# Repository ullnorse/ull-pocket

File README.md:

# ull-pocket

A pocket environment meter and learning board: ESP32-C6, temperature/humidity, pressure and motion sensors, a 1.54" e-paper display and a 1200 mAh LiPo. It sleeps most of the time; buttons, motion or a timer wake it, and Wi-Fi only runs when the firmware asks for it.

## Hardware

| Block | Part |
|---|---|
| MCU | ESP32-C6-MINI-1-N4 (Wi-Fi 6, BLE, 802.15.4, 4 MB flash) |
| Temperature / humidity | Sensirion SHT40, on a moated island away from the heat sources |
| Pressure | Bosch BMP580 |
| Motion / wake | ST LIS2DW12 accelerometer |
| Battery | 1200 mAh 1S LiPo (103040), 1.25 mm plug; MAX17048 fuel gauge; low-side reverse-polarity FET |
| Charging | TI BQ24073 power path, ~270 mA from USB-C, about 5-6 h for a full charge |
| 3.3 V | Richtek RT9080 LDO, ~2 uA quiescent |
| Display | Good Display GDEY0154D67, 200x200 black/white e-paper, SSD1681, bought separately |
| Input | 3 side buttons UP / OK / DN (UP and OK wake from deep sleep; DN doubles as BOOT) |
| LEDs | Power (green), charge (red), user (red/blue), side-view at the bottom edge |
| Programming | USB-C (native USB Serial/JTAG) or 2x3 pogo pads on the back |

Board: 40 x 44.5 mm, 4 layers, 1.6 mm (JLC04161H-3313 stackup), all parts on the front; the panel sits on the back.

## Files

| Path | Contents |
|---|---|
| `ull-pocket.kicad_pro` | KiCad 10 project (schematic + board) |
| `lib/` | Project symbols, footprints and 3D models |
| `production/` | JLCPCB Gerbers, BOM and CPL: single board (`ull-pocket-r0.9-*`) and the assembly panel (`ull-pocket-r0.9-panel-*`, made by `tools/panelize.sh`) |
| `PARTS.md` | Parts list with LCSC numbers and design notes |
| `DATASHEETS.md` | Datasheet links |
| `docs/mechanical.md` | Outline, keep-outs, panel, battery and button positions for a case |
| `docs/3d-models.md` | 3D models checked against the datasheets |
| `production/ull-pocket-r0.9-assembly.pdf` | Assembly drawing: every part with its reference. The silkscreen labels ICs, connectors, buttons, LEDs and test points only; look resistors and capacitors up here |
| `docs/learn.html` | Interactive course: understand every part of the board, from zero |
| `docs/best-practices.md` | Schematic, layout, DFM and silkscreen checklist with sources, and how this board was checked against it |
| `tools/` | Checks and exports: ERC and netlist checks, JLC export, renders (`tools/archive/` holds the retired schematic generator) |

## Ordering

Order the **panel**: one board with 5 mm rails on the left and right (tooling holes and fiducials) and mouse-bite tabs, made by `tools/panelize.sh` (needs KiKit). The rails are only left and right because parts overhang the top and bottom edges; JLC's own rails could collide with them.

1. Upload `production/ull-pocket-r0.9-panel-gerbers.zip` to JLCPCB and set:
   - 4 layers, 1.6 mm, stackup JLC04161H-3313, impedance control not needed
   - surface finish **ENIG** (the LGA/QFN/DFN parts need a flat finish; HASL is the default)
   - min via hole / diameter **0.2 / 0.45 mm**; via covering: tented
   - order number: **specify a position** (the `JLCJLCJLCJLC` text on the front silkscreen)
   - panel by customer (1 board per panel), edge rails: none (already in the files)
2. Enable PCB assembly (top side, **Standard PCBA**: U1, U3, U4 and the LEDs aren't offered on Economic) and upload `ull-pocket-r0.9-panel-bom.csv` and `ull-pocket-r0.9-panel-cpl.csv`.
3. Add a remark: "Customer panel with left/right rails and mouse bites. Components overhang the board edge: ESP32 module antenna 5.4 mm (top edge), USB-C 0.6 mm, D1/D5 LEDs 0.4 mm and RGB D6 0.65 mm (bottom edge), side buttons 0.2 mm (left edge)."
4. Check the part rotations in JLC's preview against `production/rotation-check.md`, and D1/D5/D6 against `docs/3d-models.md` (lens toward the board edge, cathode on pad 1).
5. Buy separately: the e-paper panel (GDEY0154D67), a 103040 LiPo with a protection board and 1.25 mm plug (check that it mates with J2 and its polarity: pin 2 = +), and a 3 mm thermal gap pad for TH1 (see `docs/mechanical.md`).
6. Separate boards from the rails by cutting the tabs, not bending: U1's pads and the VBAT track are about 1 mm from the holes.
7. Before first USB plug-in, check the cell's polarity. Q2 blocks a reversed cell on battery, but with USB in the charger slowly drains it through Q2.

## Programming

Plug in USB-C. The ESP32-C6 shows up as a USB serial port and esptool, Arduino or ESP-IDF flash it with no buttons: target `esp32c6` (Arduino: "ESP32C6 Dev Module", USB CDC On Boot enabled).

USB is off while the chip is in deep sleep, so keep the firmware awake while `USB_PGOOD_N` (IO1) is low (cable plugged in).

Firmware rules:
- Stop at a safe cell voltage: the cell's listing doesn't promise over-discharge protection.
- Enable the RTC watchdog: EN is only on the back pogo pads, so there's no reset button in the case.
- IO15 (CHG_DIS) high pauses charging. In deep sleep, hold it low or leave it as an input so R36 keeps charging on.
- Don't run Wi-Fi validation with no cell: the input limit leaves little margin over TX peaks.
- Ignore temperature and humidity while charging and until the case cools; measure how long that takes on the first board.

First-board power-up:
1. Power up without the panel. Check +3V3 at TP5.
2. Unpower the board, plug the panel in, and check continuity from GND (TP3) to the panel's VSS finger, the 17th from the pin-1 end. It must beep: a reversed tail would put about 20 V on the wrong panel pins.
3. Only then power up with the panel.

First-board charge test: compare TH1 with a thermocouple on the cell during a full charge. Board heat could still reach TH1's 47 C limit in a very warm room and pause charging (estimated, not measured). CHG flashing at 2 Hz means a timer fault; replug USB to clear it.

**Recovery:** if the firmware crashes, sleeps or disables USB before it can be flashed, unplug USB and the battery, hold **DN** (it is also BOOT, IO9), and plug USB back in. The chip starts in its ROM download mode; flash as usual, then reset by unplugging. The back pogo pads (J4) carry EN, BOOT and UART0 for a pogo fixture.

## Opening in KiCad

### 1. Install KiCad 10

Download KiCad 10.0 or newer from [kicad.org/download](https://www.kicad.org/download/) and use the default install, which includes the standard symbol, footprint and 3D-model libraries. KiCad 9 and older cannot open these files.

- **Windows / macOS:** run the installer.
- **Ubuntu / Debian:**
  ```sh
  sudo add-apt-repository ppa:kicad/kicad-10.0-releases
  sudo apt install kicad kicad-footprints kicad-symbols kicad-packages3d
  ```
  `kicad-packages3d` is needed for the 3D viewer.

On the very first start KiCad asks how to configure the global library tables: choose **Copy default global library table**.

### 2. Get the files

```sh
git clone https://github.com/ullnorse/ull-pocket.git
```

or use **Code → Download ZIP** on GitHub and unzip it.

### 3. Open the project

Open `ull-pocket.kicad_pro` (double-click it, or **File → Open Project** in KiCad). From the project window:

- **Schematic Editor** shows the schematic (one A3 sheet).
- **PCB Editor** shows the board. **View → 3D Viewer** (Alt+3) shows the assembled board.

No library setup is needed. The project's own symbols, footprints and 3D models are in `lib/` and are registered by the project-level `sym-lib-table` and `fp-lib-table` (paths are relative, via `${KIPRJMOD}`). Everything else comes from KiCad's standard libraries.

Keep the folder structure intact: KiCad finds `lib/` relative to the `.kicad_pro` file. If footprints or 3D models show as missing, check **Preferences → Manage Footprint Libraries → Project Specific Libraries** lists `ull-pocket` and that the folder was not moved.

### 4. Editing

- **Board:** edit freely in the PCB Editor. Run **Inspect → Design Rules Checker** before ordering. Custom rules are in `ull-pocket.kicad_dru` (side-LED edge clearance, e-paper high-voltage clearance, the thin traces on the SHT40 island, U6 thermal vias). Expect 3 harmless "footprint does not match library" warnings (C12, U1, J1) for parts edited on purpose.
- **Schematic and symbols:** edit them in the Schematic Editor and Symbol Editor. The project's symbols are in `lib/ull-pocket.kicad_sym`.
- After a schematic change, update the board with **Tools → Update PCB from Schematic** (F8) in the PCB Editor.

### 5. Regenerating production files

In KiCad: **File → Fabrication Outputs** (Gerbers, drill files, component placement). The JLCPCB-formatted files in `production/` are made by scripts, on Linux with KiCad 10 and Python 3:

```sh
sh tools/jlc_export.sh                     # Gerbers + drill files -> production/*-gerbers.zip
python3 tools/jlc_cpl.py ull-pocket.kicad_pcb <easyeda-cache> production   # BOM + CPL with JLC rotations
sh tools/panelize.sh                       # assembly panel -> build/panel/ull-pocket-panel.kicad_pcb (pipx install kikit)
sh tools/jlc_export.sh build/panel/ull-pocket-panel.kicad_pcb ull-pocket-r0.9-panel
python3 tools/jlc_cpl.py build/panel/ull-pocket-panel.kicad_pcb <easyeda-cache> production ull-pocket-r0.9-panel
python3 tools/silk/assembly.py ull-pocket.kicad_pcb production/ull-pocket-r0.9-assembly.pdf
sh tools/check_sch.sh                      # ERC, netlist checks, pin/pad checks, schematic PDF + PNG
sh tools/render3d.sh                       # 3D renders -> build/render3d/
```

`jlc_cpl.py` compares each footprint with JLC's own (EasyEDA) footprint to get placement rotations; fetch those once per LCSC part with `easyeda2kicad --footprint --lcsc_id=Cxxx --output=<easyeda-cache>/Cxxx/lib` (`pip install easyeda2kicad`). `check_sch.sh` also needs `rsvg-convert` (`sudo apt install librsvg2-bin`). `tools/check_net.py` encodes the intended connections; update it when you change the circuit on purpose.

## License

CERN-OHL-P v2, see [LICENSE](LICENSE).

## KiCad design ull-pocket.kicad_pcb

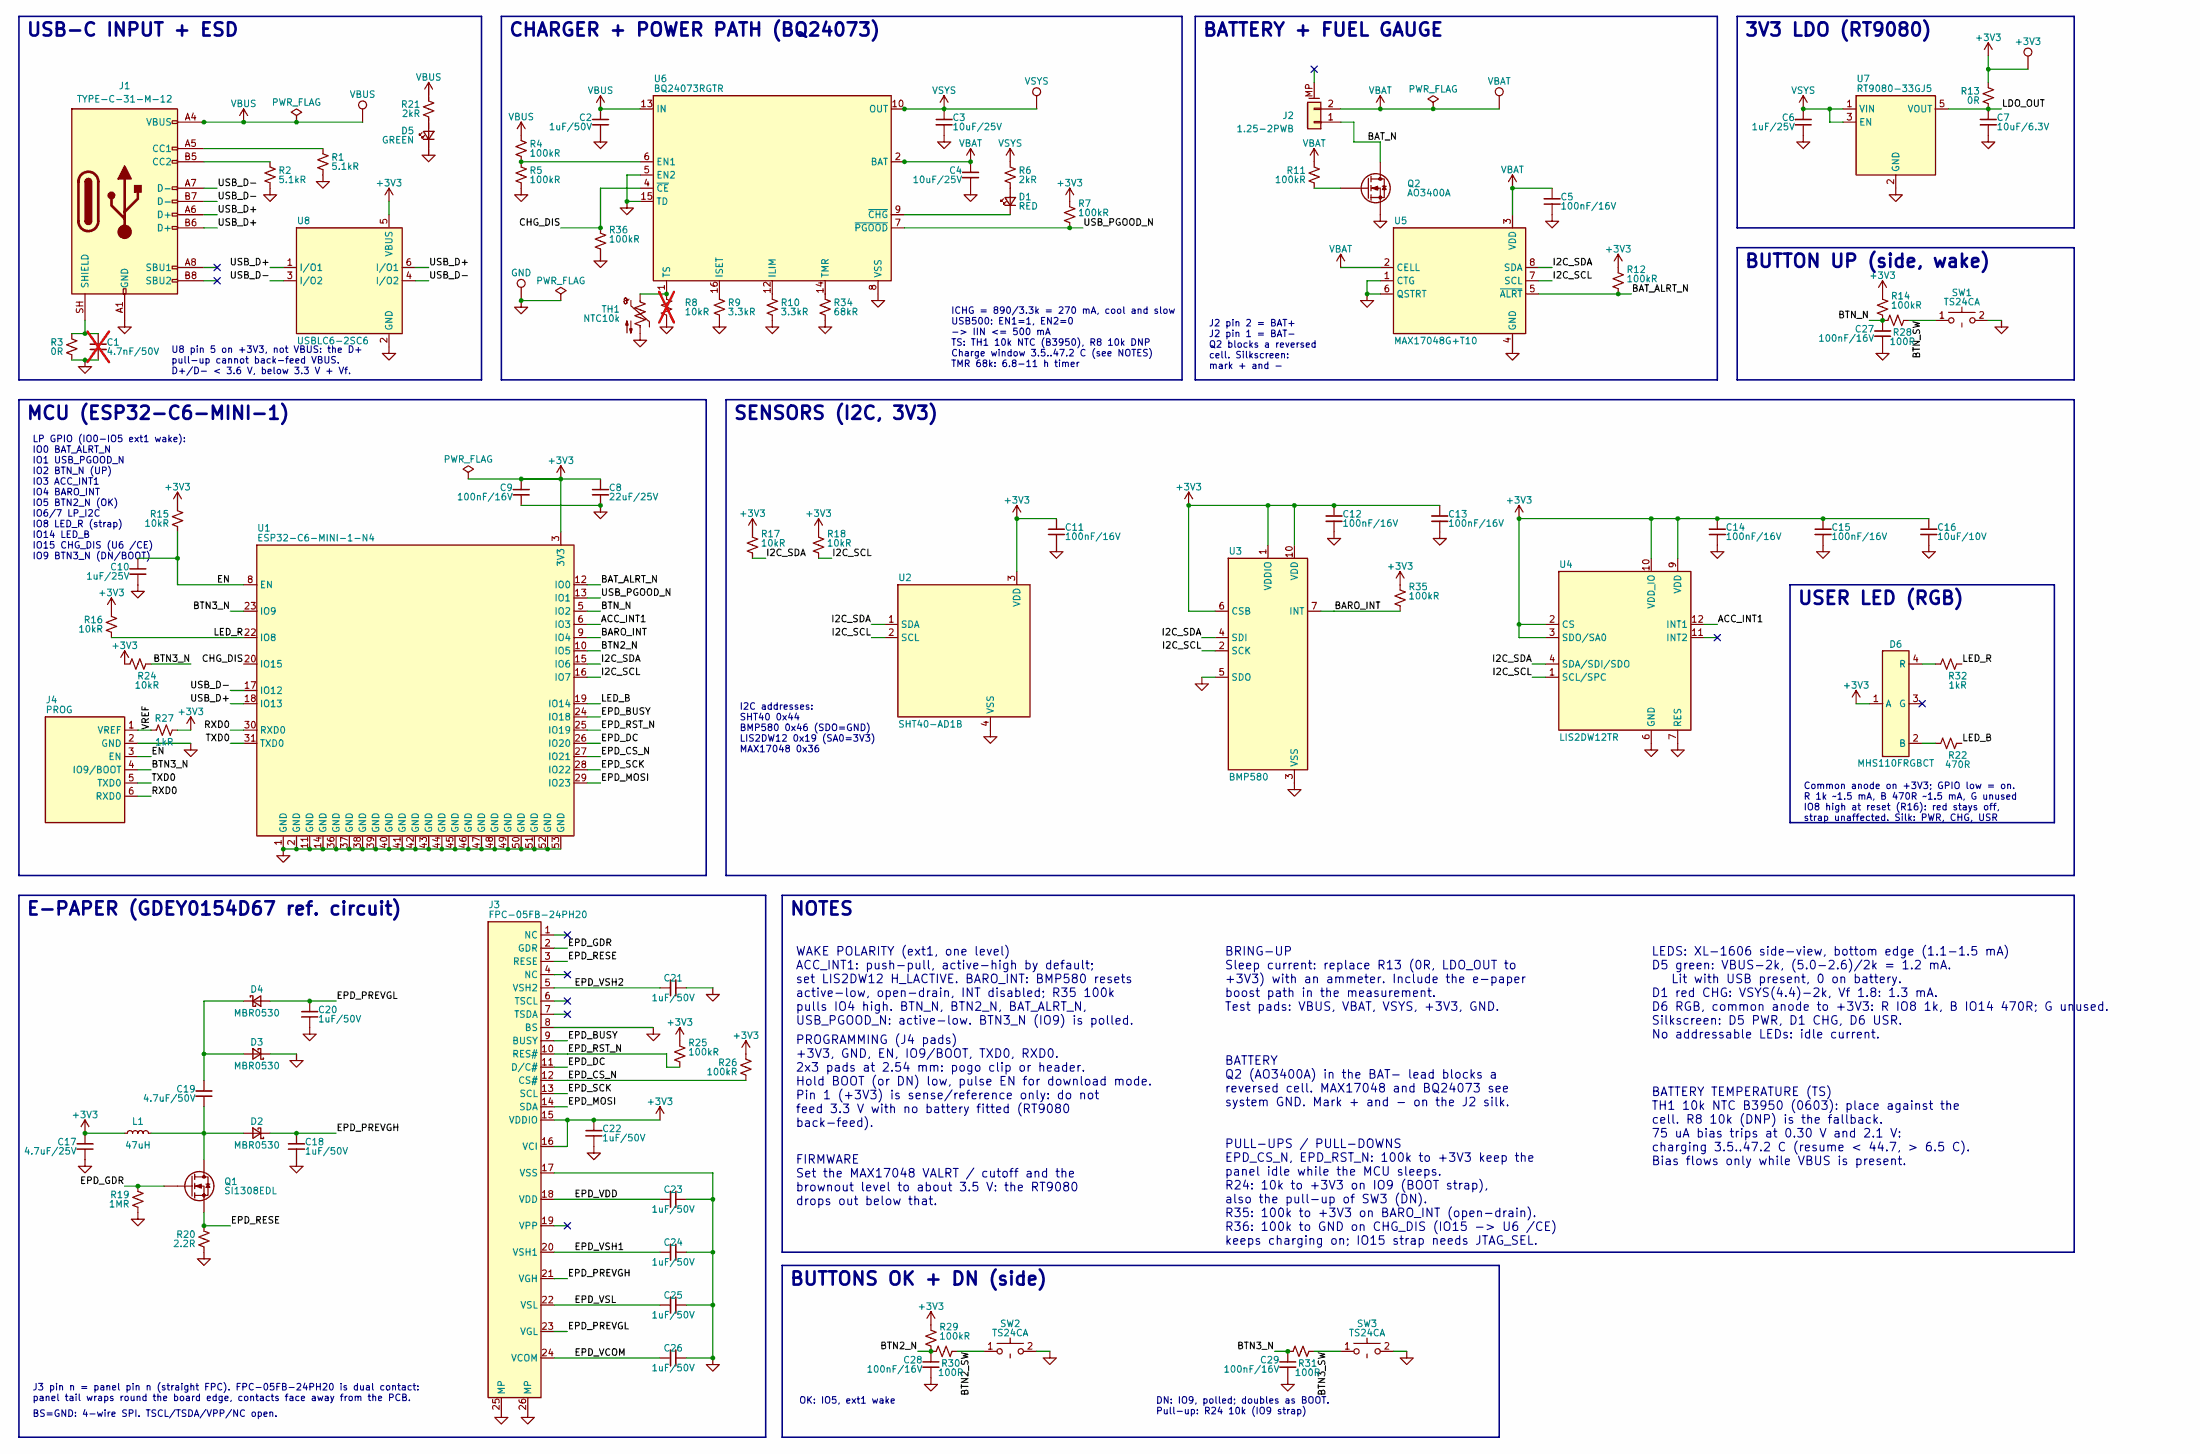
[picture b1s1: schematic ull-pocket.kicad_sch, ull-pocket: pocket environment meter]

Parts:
C1: 4.7nF/50V; C_0402_1005Metric; MPN 0402B472K500NT; LCSC C1538; not fitted
C2, C18, C20, C21, C22, C23, C24, C25, C26: 1uF/50V; C_0603_1608Metric; MPN CL10A105KB8NNNC; LCSC C15849
C3, C4: 10uF/25V; C_0805_2012Metric; MPN CL21A106KAYNNNE; LCSC C15850
C5, C9, C11, C12, C13, C14, C15, C27, C28, C29: 100nF/16V; C_0402_1005Metric; MPN CL05B104KO5NNNC; LCSC C1525
C6, C10: 1uF/25V; C_0402_1005Metric; MPN CL05A105KA5NQNC; LCSC C52923
C7: 10uF/6.3V; C_0402_1005Metric; MPN CL05A106MQ5NUNC; LCSC C15525
C8: 22uF/25V; C_0805_2012Metric; MPN CL21A226MAQNNNE; LCSC C45783
C16: 10uF/10V; C_0603_1608Metric; MPN CL10A106KP8NNNC; LCSC C19702
C17: 4.7uF/25V; C_0805_2012Metric; MPN CL21A475KAQNNNE; LCSC C1779
C19: 4.7uF/50V; C_0805_2012Metric; MPN CL21A475KBQNNNE; LCSC C98192
D1: RED; LED_XL-1606_SideView; MPN XL-1606SURC; LCSC C965860
D2, D3, D4: MBR0530; D_SOD-123; MPN MBR0530T1G; LCSC C82046
D5: GREEN; LED_XL-1606_SideView; MPN XL-1606UGC; LCSC C965863
D6: MHS110FRGBCT; LED_MHS110FRGBCT_SideView; MPN MHS110FRGBCT; LCSC C496820
J1: TYPE-C-31-M-12; USB_C_Receptacle_HRO_TYPE-C-31-M-12; MPN TYPE-C-31-M-12; LCSC C165948
J2: 1.25-2PWB; Molex_PicoBlade_53261-0271_1x02-1MP_P1.25mm_Horizontal; MPN 1.25-2PWB; LCSC C2905009
J3: FPC-05FB-24PH20; FPC-SMD_24P-P0.50_FPC-05FB-24PH20; MPN FPC-05FB-24PH20; LCSC C2856831
J4: PROG; PogoPads_2x3_P2.54mm_D1.0; MPN PROG
L1: 47uH; IND-SMD_L4.0-W4.0_FNR40XXS; MPN FNR4030S470MT; LCSC C167888
Q1: SI1308EDL; SOT-323_SC-70; MPN SI1308EDL-T1-GE3; LCSC C469327
Q2: AO3400A; SOT-23; MPN AO3400A; LCSC C20917
R1, R2: 5.1kR; R_0402_1005Metric; MPN 0402WGF5101TCE; LCSC C25905
R3: 0R; R_0402_1005Metric; MPN 0402WGF0000TCE; LCSC C17168
R4, R5, R7, R11, R12, R14, R25, R26, R29, R35, R36: 100kR; R_0402_1005Metric; MPN 0402WGF1003TCE; LCSC C25741
R6, R21: 2kR; R_0402_1005Metric; MPN 0402WGF2001TCE; LCSC C4109
R8: 10kR; R_0402_1005Metric; MPN 0402WGF1002TCE; LCSC C25744; not fitted
R9, R10: 3.3kR; R_0402_1005Metric; MPN 0402WGF3301TCE; LCSC C25890
R13: 0R; R_0603_1608Metric; MPN 0603WAF0000T5E; LCSC C21189
R15, R16, R17, R18, R24: 10kR; R_0402_1005Metric; MPN 0402WGF1002TCE; LCSC C25744
R19: 1MR; R_0603_1608Metric; MPN 0603WAF1004T5E; LCSC C22935
R20: 2.2R; R_0603_1608Metric; MPN 0603WAF220KT5E; LCSC C22939
R22: 470R; R_0402_1005Metric; MPN 0402WGF4700TCE; LCSC C25117
R27, R32: 1kR; R_0402_1005Metric; MPN 0402WGF1001TCE; LCSC C11702
R28, R30, R31: 100R; R_0402_1005Metric; MPN 0402WGF1000TCE; LCSC C25076
R34: 68kR; R_0402_1005Metric; MPN 0402WGF6802TCE; LCSC C36871
SW1, SW2, SW3: TS24CA; SW-SMD_2P-TS24CA; MPN TS24CA; LCSC C393942
TH1: NTC10k; R_0603_1608Metric; MPN SDNT1608X103F3950FTF; LCSC C279936
TP1: VBUS; TestPoint_Pad_1.0x1.0mm
TP2: VSYS; TestPoint_Pad_1.0x1.0mm
TP3: GND; TestPoint_Pad_1.0x1.0mm
TP4: VBAT; TestPoint_Pad_1.0x1.0mm
TP5: +3V3; TestPoint_Pad_1.0x1.0mm
U1: ESP32-C6-MINI-1-N4; ESP32-C6-MINI-1; MPN ESP32-C6-MINI-1-N4; LCSC C5736265
U2: SHT40-AD1B; Sensirion_DFN-4_1.5x1.5mm_P0.8mm_SHT4x; MPN SHT40-AD1B-R2; LCSC C2909890
U3: BMP580; Bosch_LGA-10_2x2mm_P0.5mm_BMP580; MPN BMP580; LCSC C22391138
U4: LIS2DW12TR; LGA-12_2x2mm_P0.5mm; MPN LIS2DW12TR; LCSC C189624
U5: MAX17048G+T10; TDFN-8_L2.0-W2.0-P0.50-BL-EP1.2; MPN MAX17048G+T10; LCSC C2682616
U6: BQ24073RGTR; VQFN-16-1EP_3x3mm_P0.5mm_EP1.68x1.68mm; MPN BQ24073RGTR; LCSC C15220
U7: RT9080-33GJ5; TSOT-23-5; MPN RT9080-33GJ5; LCSC C841192
U8: USBLC6-2SC6; SOT-23-6; MPN USBLC6-2SC6; LCSC C2687116

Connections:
+3V3: C8.1, C9.1, C11.1, C12.1, C13.1, C14.1, C15.1, C16.1, C17.1, C22.1, D6.1 (A), J3.15 (VDDIO), J3.16 (VCI), L1.1, R7.1, R12.1, R13.1, R14.1, R15.1, R16.1, R17.1, R18.1, R24.1, R25.1, R26.1, R27.2, R29.1, R35.1, TP5.1 (1_1), U1.3 (3V3), U2.3 (VDD), U3.1 (VDDIO), U3.6 (CSB), U3.10 (VDD), U4.2 (CS), U4.3 (SDO/SA0), U4.9 (VDD), U4.10 (VDD_IO), U8.5 (VBUS)
/ACC_INT1: U1.6 (IO3), U4.12 (INT1)
/BARO_INT: R35.2, U1.9 (IO4), U3.7 (INT)
/BAT_ALRT_N: R12.2, U1.12 (IO0), U5.5 (~ALRT)
/BAT_N: J2.1, Q2.3 (D)
/BTN2_N: C28.1, R29.2, R30.1, U1.10 (IO5)
/BTN2_SW: R30.2, SW2.1
/BTN3_N: C29.1, J4.4 (IO9/BOOT), R24.2, R31.1, U1.23 (IO9)
/BTN3_SW: R31.2, SW3.1
/BTN_N: C27.1, R14.2, R28.1, U1.5 (IO2)
/BTN_SW: R28.2, SW1.1
/CHG_DIS: R36.1, U1.20 (IO15), U6.4 (~CE)
/EN: C10.1, J4.3 (EN), R15.2, U1.8 (EN)
/EPD_BUSY: J3.9 (BUSY), U1.24 (IO18)
/EPD_CS_N: J3.12 (CS#), R26.2, U1.27 (IO21)
/EPD_DC: J3.11 (D/C#), U1.26 (IO20)
/EPD_GDR: J3.2 (GDR), Q1.1 (G), R19.1
/EPD_MOSI: J3.14 (SDA), U1.29 (IO23)
/EPD_PREVGH: C18.1, D2.1 (K), J3.21 (VGH)
/EPD_PREVGL: C20.1, D4.2 (A), J3.23 (VGL)
/EPD_RESE: J3.3 (RESE), Q1.2 (S), R20.1
/EPD_RST_N: J3.10 (RES#), R25.2, U1.25 (IO19)
/EPD_SCK: J3.13 (SCL), U1.28 (IO22)
/EPD_VCOM: C26.1, J3.24 (VCOM)
/EPD_VDD: C23.1, J3.18 (VDD)
/EPD_VSH1: C24.1, J3.20 (VSH1)
/EPD_VSH2: C21.1, J3.5 (VSH2)
/EPD_VSL: C25.1, J3.22 (VSL)
/I2C_SCL: R18.2, U1.16 (IO7), U2.2 (SCL), U3.2 (SCK), U4.1 (SCL/SPC), U5.7 (SCL)
/I2C_SDA: R17.2, U1.15 (IO6), U2.1 (SDA), U3.4 (SDI), U4.4 (SDA/SDI/SDO), U5.8 (SDA)
/LDO_OUT: C7.1, R13.2, U7.5 (VOUT)
/LED_B: R22.1, U1.19 (IO14)
/LED_R: R16.2, R32.1, U1.22 (IO8)
/RXD0: J4.6 (RXD0), U1.30 (RXD0)
/TXD0: J4.5 (TXD0), U1.31 (TXD0)
/USB_D+: J1.A6 (D+), J1.B6 (D+), U1.18 (IO13), U8.1 (I/O1), U8.6 (I/O1)
/USB_D-: J1.A7 (D-), J1.B7 (D-), U1.17 (IO12), U8.3 (I/O2), U8.4 (I/O2)
/USB_PGOOD_N: R7.2, U1.13 (IO1), U6.7 (~PGOOD)
/VREF: J4.1 (+3V3), R27.1
GND: C1.2, C2.2, C3.2, C4.2, C5.2, C6.2, C7.2, C8.2, C9.2, C10.2, C11.2, C12.2, C13.2, C14.2, C15.2, C16.2, C17.2, C18.2, C20.2, C21.2, C22.2, C23.2, C24.2, C25.2, C26.2, C27.2, C28.2, C29.2, D3.1 (K), D5.1 (K), J1.A1 (GND), J1.A12 (GND), J1.B1 (GND), J1.B12 (GND), J3.8 (BS), J3.17 (VSS), J3.25 (MP), J3.26 (MP), J4.2 (GND), Q2.2 (S), R1.2, R2.2, R3.2, R5.2, R8.2, R9.2, R10.2, R19.2, R20.2, R34.2, R36.2, SW1.2, SW2.2, SW3.2, TH1.2, TP3.1 (1_1), U1.1 (GND), U1.2 (GND), U1.11 (GND), U1.14 (GND), U1.36 (GND), U1.37 (GND), U1.38 (GND), U1.39 (GND), U1.40 (GND), U1.41 (GND), U1.42 (GND), U1.43 (GND), U1.44 (GND), U1.45 (GND), U1.46 (GND), U1.47 (GND), U1.48 (GND), U1.49 (GND), U1.50 (GND), U1.51 (GND), U1.52 (GND), U1.53 (GND), U2.4 (VSS), U3.3 (VSS), U3.5 (SDO), U3.8 (VSS), U3.9 (VSS), U4.6 (GND), U4.7 (RES), U4.8 (GND), U5.1 (CTG), U5.4 (GND), U5.6 (QSTRT), U5.9 (GND), U6.5 (EN2), U6.8 (VSS), U6.15 (TD), U6.17 (VSS), U7.2 (GND), U8.2 (GND)
unnamed: D1.2 (A), R6.2
unnamed: D1.1 (K), U6.9 (~CHG)
unnamed: C19.2, D2.2 (A), L1.2, Q1.3 (D)
unnamed: C19.1, D3.2 (A), D4.1 (K)
unnamed: D5.2 (A), R21.2
unnamed: D6.2 (B), R22.2
unnamed: D6.4 (R), R32.2
unnamed: J1.A5 (CC1), R1.1
unnamed: J1.B5 (CC2), R2.1
unnamed: C1.1, J1.SH (SHIELD), R3.1
unnamed: Q2.1 (G), R11.2
unnamed: R4.2, R5.1, U6.6 (EN1)
unnamed: R10.1, U6.12 (ILIM)
unnamed: R9.1, U6.16 (ISET)
unnamed: R34.1, U6.14 (TMR)
unnamed: R8.1, TH1.1, U6.1 (TS)
VBAT: C4.1, C5.1, J2.2, R11.1, TP4.1 (1_1), U5.2 (CELL), U5.3 (VDD), U6.2 (BAT), U6.3 (BAT)
VBUS: C2.1, J1.A4 (VBUS), J1.A9 (VBUS), J1.B4 (VBUS), J1.B9 (VBUS), R4.1, R21.1, TP1.1 (1_1), U6.13 (IN)
VSYS: C3.1, C6.1, R6.1, TP2.1 (1_1), U6.10 (OUT), U6.11 (OUT), U7.1 (VIN), U7.3 (EN)

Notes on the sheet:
BS=GND: 4-wire SPI. TSCL/TSDA/VPP/NC open.
PULL-UPS / PULL-DOWNS EPD_CS_N, EPD_RST_N: 100k to +3V3 keep the panel idle while the MCU sleeps. R24: 10k to +3V3 on IO9 (BOOT strap), also the pull-up of SW3 (DN). R35: 100k to +3V3 on BARO_INT (open-drain). R36: 100k to GND on CHG_DIS (IO15 -> U6 /CE) keeps charging on; IO15 strap needs JTAG_SEL.
BATTERY + FUEL GAUGE
NOTES
ICHG = 890/3.3k = 270 mA, cool and slow USB500: EN1=1, EN2=0 -> IIN <= 500 mA TS: TH1 10k NTC (B3950), R8 10k DNP Charge window 3.5..47.2 C (see NOTES) TMR 68k: 6.8-11 h timer
I2C addresses: SHT40 0x44 BMP580 0x46 (SDO=GND) LIS2DW12 0x19 (SA0=3V3) MAX17048 0x36
E-PAPER (GDEY0154D67 ref. circuit)
MCU (ESP32-C6-MINI-1)
USB-C INPUT + ESD
OK: IO5, ext1 wake
LEDS: XL-1606 side-view, bottom edge (1.1-1.5 mA) D5 green: VBUS-2k, (5.0-2.6)/2k = 1.2 mA. Lit with USB present, 0 on battery. D1 red CHG: VSYS(4.4)-2k, Vf 1.8: 1.3 mA. D6 RGB, common anode to +3V3: R IO8 1k, B IO14 470R; G unused. Silkscreen: D5 PWR, D1 CHG, D6 USR. No addressable LEDs: idle curr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
J2 pin 2 = BAT+ J2 pin 1 = BAT- Q2 blocks a reversed cell. Silkscreen: mark + and -
J3 pin n = panel pin n (straight FPC). FPC-05FB-24PH20 is dual contact: panel tail wraps round the board edge, contacts face away from the PCB.
SENSORS (I2C, 3V3)
CHARGER + POWER PATH (BQ24073)
WAKE POLARITY (ext1, one level) ACC_INT1: push-pull, active-high by default; set LIS2DW12 H_LACTIVE. BARO_INT: BMP580 resets active-low, open-drain, INT disabled; R35 100k pulls IO4 high. BTN_N, BTN2_N, BAT_ALRT_N, USB_PGOOD_N: active-low. BTN3_N (IO9) is polled.
USER LED (RGB)
DN: IO9, polled; doubles as BOOT. Pull-up: R24 10k (IO9 strap)
BUTTONS OK + DN (side)
PROGRAMMING (J4 pads) +3V3, GND, EN, IO9/BOOT, TXD0, RXD0. 2x3 pads at 2.54 mm: pogo clip or header. Hold BOOT (or DN) low, pulse EN for download mode. Pin 1 (+3V3) is sense/reference only: do not feed 3.3 V with no battery fitted (RT9080 back-feed).
BATTERY TEMPERATURE (TS) TH1 10k NTC B3950 (0603): place against the cell. R8 10k (DNP) is the fallback. 75 uA bias trips at 0.30 V and 2.1 V: charging 3.5..47.2 C (resume < 44.7, > 6.5 C). Bias flows only while VBUS is present.
BATTERY Q2 (AO3400A) in the BAT- lead blocks a reversed cell. MAX17048 and BQ24073 see system GND. Mark + and - on the J2 silk.
3V3 LDO (RT9080)
BUTTON UP (side, wake)
BRING-UP Sleep current: replace R13 (0R, LDO_OUT to +3V3) with an ammeter. Include the e-paper boost path in the measurement. Test pads: VBUS, VBAT, VSYS, +3V3, GND.
FIRMWARE Set the MAX17048 VALRT / cutoff and the brownout level to about 3.5 V: the RT9080 drops out below that.
LP GPIO (IO0-IO5 ext1 wake): IO0 BAT_ALRT_N IO1 USB_PGOOD_N IO2 BTN_N (UP) IO3 ACC_INT1 IO4 BARO_INT IO5 BTN2_N (OK) IO6/7 LP_I2C IO8 LED_R (strap) IO14 LED_B IO15 CHG_DIS (U6 /CE) IO9 BTN3_N (DN/BOOT)
Common anode on +3V3; GPIO low = on. R 1k ~1.5 mA, B 470R ~1.5 mA, G unused IO8 high at reset (R16): red stays off, strap unaffected. Silk: PWR, CHG, USR
U8 pin 5 on +3V3, not VBUS: the D+ pull-up cannot back-feed VBUS. D+/D- < 3.6 V, below 3.3 V + Vf.

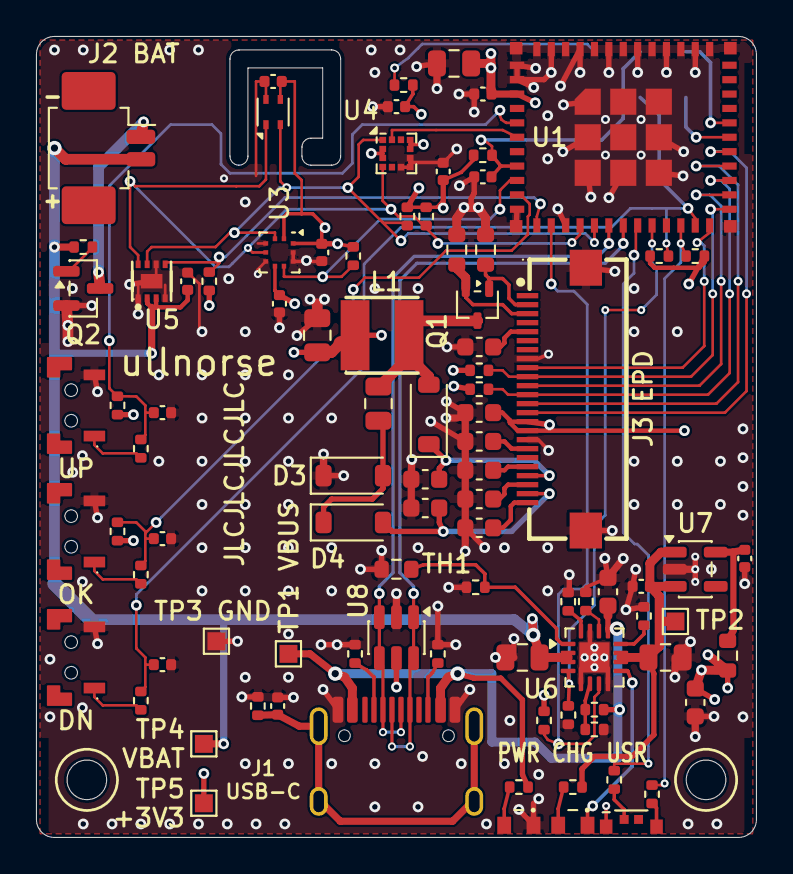
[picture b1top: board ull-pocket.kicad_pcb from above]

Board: 4 copper layers, 40.0 x 44.5 mm, 97 parts (1 on the bottom side), 59 nets.

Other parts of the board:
ASSY1: ASSY_GDEY0154D67_Panel
ASSY2: ASSY_LiPo_103040
H1, H2: MountingHole_2.2mm_M2

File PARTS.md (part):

# ull-pocket parts, rev 0.9 (2026-11-09) (stock checked on JLCPCB via pcbparts.dev, 2026-10-28; LEDs 2026-10-29)

| Ref | Function | Part | LCSC | Package | Note |
|---|---|---|---|---|---|
| U1 | MCU + Wi-Fi/BLE/802.15.4 | ESP32-C6-MINI-1-N4 | C5736265 | 16.6x13.2 module, PCB antenna | 4 MB flash, -40..85 C (rev 0.7: was the 105 C -H4 C6553337, 569 in stock); antenna at board edge with keep-out |
| U2 | Temp / RH | SHT40-AD1B | C2909890 | DFN-4 1.5x1.5, P0.8 (`ull-pocket:Sensirion_DFN-4_1.5x1.5mm_P0.8mm_SHT4x`, 4 pads) | I2C 0x44; on the moated, thermally isolated island at the top edge, joined by thin bridge tracks; C11 decoupling sits on the island; the centre pad is not used (Sensirion allows it floating). Replaces SHT31-DIS-B2.5kS C80862 (rev 0.8) |
| U3 | Pressure | BMP580 | C22391138 | LGA-10 2x2, P0.5 (`ull-pocket:Bosch_LGA-10_2x2mm_P0.5mm_BMP580`) | I2C 0x46 (SDO to GND), CSB to +3V3 for I2C mode. Replaces BMP585 C18184976 (rev 0.8); the BMP585 mask-opening/keepout rule area is gone. INT resets active-low, open-drain, disabled (INT_CONFIG 0x14 = 0x35, datasheet p.53); R35 100k pulls BARO_INT high. Keep it open-drain, active-low in firmware |
| U4 | Accelerometer | LIS2DW12TR | C189624 | LGA-12 2x2, P0.5 (stock `Package_LGA:LGA-12_2x2mm_P0.5mm`) | I2C 0x19 (SA0 and CS to +3V3); INT1 to ACC_INT1 (LP GPIO) for wake. INT1 is push-pull active-high by default: set CTRL3 H_LACTIVE for active-low. Replaces LIS3DHTR C15134 (rev 0.8) |
| U5 | Fuel gauge | MAX17048G+T10 | C2682616 | DFN-8 2x2 | |
| U6 | Li-ion charger, power path | BQ24073RGTR | C15220 | VQFN-16 3x3, EP 1.68 (stock `VQFN-16-1EP_3x3mm_P0.5mm_EP1.68x1.68mm`) | 4.4 V OUT regulation; replaces BQ24074 (17 in stock). /CE (pin 4) on CHG_DIS from IO15 (rev 0.9; was GND): high pauses charging, OUT and battery supplement keep working (datasheet p.8); VIH 1.4 V, VIL 0.4 V (p.14) |
| U7 | 3.3 V LDO, ~2 uA Iq, 600 mA | RT9080-33GJ5 | C841192 | TSOT-23-5 | |
| C2 | U6 IN cap | CL10A105KB8NNNC 1uF/50V X5R | C15849 | 0603 | was 1uF/25V 0402 (C52923); 50 V rating for VBUS transients, basic part, 13M in stock |
| Q2 | Battery reverse-polarity FET (low side, BAT- lead) | AO3400A | C20917 | SOT-23 | basic part, 1.13M in stock; Vgs(max) 12 V; drain = BAT_N (J2 pin 1), source = GND, gate = VBAT via R11 100k |
| R13 | Sleep-current link, LDO_OUT to +3V3 | 0603WAF0000T5E 0R | C21189 | 0603 | basic part, 21.6M in stock; replace with an ammeter to measure sleep current |
| TP1-TP5 | Test pads: VBUS, VSYS, GND, VBAT, +3V3 (TP6 SPARE_IO14 removed in rev 0.6: IO14 drives the user LED) | TestPoint_Pad_1.0x1.0mm | - | 1.0 mm pad | footprint only, excluded from BOM |
| J4 | PROG pogo pads: VREF, GND, EN, IO9/BOOT (net BTN3_N, shared with SW3 DN), TXD0, RXD0 | PogoPads_2x3_P2.54mm_D1.0 | - | 2x3 grid, 2.54 mm pitch, 1.0 mm round SMD pads | footprint only, excluded from BOM and placement; on B.Cu above the panel; mates with a 2x3 pogo fixture (no room for a header); pad 1 is VREF, a sense-only reference fed from +3V3 through R27 1k: the programmer cannot power the board. Power from USB or the battery while programming |
| R27 | J4.1 VREF series resistor, +3V3 to J4 pad 1 | 0402WGF1001TCE 1k | C11702 | 0402 | basic; on F left of U1 at (20.4, 2.7), via + B.Cu run to the pad; limits programmer back-feed to ~1 mA |
| R3 | USB-C shield to GND | 0402WGF0000TCE 0R | C17168 | 0402 | basic; plastic case, shield tied straight to GND (was 1M) |
| C1 | USB-C shield RC option | 0402B472K500NT 4.7nF/50V | C1538 | 0402 | DNP; excluded from BOM and placement; footprint kept for a metal-case RC option |
| R28 + C27 | SW1 (UP) series resistor (switch side BTN_SW) + BTN_N debounce cap to GND | 0402WGF1000TCE 100R / CL05B104KO5NNNC 100nF | C25076 / C1525 | 0402 | basic; right of SW1; R28 limits ESD current into IO2; press discharges C27 in ~10 us through R28, release recharges it through R14 100k (tau 10 ms) |
| C7 | U7 output | CL05A106MQ5NUNC 10uF/6.3V X5R | C15525 | 0402 | basic; RT9080 needs 1 uF effective on its own while R13 is swapped for an ammeter |
| R9 | U6 ISET, charge current | 0402WGF3301TCE 3.3k 1% | C25890 | 0402 | 890/3.3k = 270 mA (241 mA min); chosen for low heat |
| R34 | U6 TMR, safety timer | 0402WGF6802TCE 68k 1% | C36871 | 0402 | 10 x KTMR x 68k = 6.8-11.3 h fast charge, 41-68 min pre-charge; outlasts a full 270 mA charge |
| C8 | U1 3V3 bulk | CL21A226MAQNNNE 22uF/25V X5R | C45783 | 0805 | basic, 4.05M in stock |
| C3, C4 | U6 OUT (VSYS) and BAT caps | CL21A106KAYNNNE 10uF/25V X5R | C15850 | 0805 | basic, 8.7M in stock (2026-11-09); was 10uF/10V 0603 until rev 0.9: the 0805 keeps more capacitance at 4.2-4.4 V bias. The 16 V C1713 is an extended part, so not used |
| C19 | E-paper boost coupling cap | CL21A475KBQNNNE 4.7uF/50V X5R | C98192 | 0805 | extended, 366k in stock |
| R25, R26 | 100k pull-ups to +3V3 on EPD_RST_N, EPD_CS_N (panel idle in sleep) | 0402WGF1003TCE | C25741 | 0402 | basic |
| R35 | 100k pull-up to +3V3 on BARO_INT (IO4), for the BMP580's open-drain INT | 0402WGF1003TCE | C25741 | 0402 | basic; IO4 is the MTMS strap, which only picks the SDIO sampling edge, so a pull-up is harmless (ESP32-C6 datasheet Table 3-1, p.33) |
| R36 | 100k pull-down to GND on CHG_DIS (IO15 to U6 /CE) | 0402WGF1003TCE | C25741 | 0402 | basic; under U6 pin 4. Keeps charging on through reset and whenever IO15 is an input: IO15 resets as input with no pull (ESP32-C6 datasheet Table 2-1, p.17). As a JTAG-source strap it reads 0, which only matters if EFUSE_JTAG_SEL_ENABLE is burned (Table 3-7, p.36). IO15 high draws ~45 uA: R36 plus /CE's own ~285k pull-down (BQ24073 datasheet p.8) |
| R24 | IO9 (BOOT strap) 10k pull-up to +3V3; also the SW3 (DN) pull-up, net BTN3_N | 0402WGF1002TCE | C25744 | 0402 | basic |
| U8 | USB ESD | USBLC6-2SC6 | C2687116 | SOT-23-6 | pin 5 (VBUS rail of the diode array) on +3V3, not VBUS (rev 0.9): the D+ pull-up can't back-feed VBUS through the upper diode on battery. D+/D- stay below 3.6 V, under 3.3 V + Vf, so the diodes stay off in normal use. VBUS keeps C2 1uF/50V; the BQ24073 IN is rated to 28 V |
| J1 | USB-C | TYPE-C-31-M-12 | C165948 | 16-pin SMD | 5.1k CC pull-downs |
| J2 | Battery | 1.25-2PWB (DEALON) | C2905009 | 1.25 mm 2P SMD, right angle | extended; 174k in stock, $0.03; JLC series PicoBlade (MX 1.25), 1 A, 3.6 mm tall, -25..+85 C. Footprint: Molex 53261 land, same pad layout as the DEALON drawing. Sized for the 103040 cell's "PH-1.25" plug; confirm that plug mates before ordering. Pin 2 = BAT+, pin 1 = BAT- (via Q2); confirm the cell's polarity with a multimeter. Mouth faces the left board edge, "-" above it, "+" below |
| J3 | E-paper FPC | FPC-05FB-24PH20 | C2856831 | 24P 0.5 mm, back flip, dual contact, H2.0 | panel tail wraps round the board edge so its fingers (display side) face away from the PCB; FPC-05F-24PH20 (C2856805) is bottom-contact and would mirror the pin order. Straight map: J3 pin n = panel pin n. See docs/mechanical.md |
| SW1, SW2, SW3 | Side buttons UP / OK / DN | TS24CA (side-actuated, right-angle SMD) | C393942 | 4.6x1.8 | left edge, 7.0 mm pitch (see docs/mechanical.md); SW1 UP on IO2 (BTN_N) and SW2 OK on IO5 (BTN2_N) wake from deep sleep, SW3 DN on IO9 (BTN3_N, rev 0.7; was IO15) is polled and doubles as BOOT; locating pegs are 0.7 mm NPTH holes (no pad) |
| R29, R30 + C28 | SW2 (OK) pull-up 100k to +3V3, series 100R (switch side BTN2_SW), BTN2_N debounce 100nF | 0402WGF1003TCE / 0402WGF1000TCE / CL05B104KO5NNNC | C25741 / C25076 / C1525 | 0402 | basic; same circuit as SW1 (R14/R28/C27) |
| R31 + C29 | SW3 (DN) series 100R (switch side BTN3_SW), BTN3_N debounce 100nF | 0402WGF1000TCE / CL05B104KO5NNNC | C25076 / C1525 | 0402 | basic; pull-up is R24 10k (IO9 strap): 10k x 100n = 1 ms, well inside the 10 ms EN delay, so IO9 reads high at reset unless DN is held |
| Q1 | E-paper boost switch | SI1308EDL-T1-GE3 | C469327 | SOT-323 | per panel reference circuit |
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
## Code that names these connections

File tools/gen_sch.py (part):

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    res_up("100k", n_pg, "+3V3", side="RU")
    e_pg = add(n_pg, (1, 0), 2.54)
    wire(n_pg, e_pg)
    label("USB_PGOOD_N", e_pg, "R")
    # bottom: TS 10k (no NTC), ISET 3.3k, ILIM 3.3k, TMR open (default timers), VSS
    # TS: 10k NTC (103AT type, B=3435) left of the pin, DNP fixed 10k fallback (R8) in parallel
    p_ts = u6.p("1")
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                    "Value": (bx + 40.64, by + 33.909, "left")})
    d_q = q2.p("3")
    wire(p_bn, (p_bn[0] + 2.54, p_bn[1]), (p_bn[0] + 2.54, by + 24.13), (d_q[0], by + 24.13), d_q)
    label("BAT_N", (p_bn[0] + 5.08, by + 24.13), "R")
    pwr("GND", q2.p("2"))
    g_q = q2.p("1")
    n_g = add(g_q, (-1, 0), 5.08)
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    res_up("100k", n_al, "+3V3", side="RU")
    e_al = add(n_al, (1, 0), 2.54)
    wire(n_al, e_al)
    label("BAT_ALRT_N", e_al, "R")
    pwr("GND", u5.p("4"))

    # ============================ 3V3 LDO ==============================
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    r0 = R("0R", (n_vo[0], n_vo[1] - G), "V", "L")
    e_lo = add(n_vo, (1, 0), 2.54)
    wire(n_vo, e_lo)
    label("LDO_OUT", e_lo, "R")
    top = r0.p(1)
    n3 = add(top, (0, -1), 5.08)
    wire(top, n3)
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    res_up("100k", n1, "+3V3", side="RU")
    e1 = add(n1, (-1, 0), 2.54)
    wire(n1, e1)
    label("BTN_N", e1, "L")
    p2 = sw1.p("2")
    n2 = add(p2, (1, 0), 2.54)
    wire(p2, n2)
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                   ("25", "EPD_RST_N"), ("26", "EPD_DC"), ("27", "EPD_CS_N"), ("28", "EPD_SCK"),
                   ("29", "EPD_MOSI"), ("10", "BTN2_N"), ("19", "LED_USER")):
        stub(u1, pn, nm)
    note("LP GPIO (IO0-IO5 ext1 wake):\\nIO0 BAT_ALRT_N\\nIO1 USB_PGOOD_N\\nIO2 BTN_N (UP)\\nIO3 ACC_INT1\\n"
         "IO4 BARO_INT\\nIO5 BTN2_N (OK)\\nIO6/7 LP_I2C\\nIO8 10k pull-up\\nIO14 LED_USER\\nIO15 BTN3_N (DN, no wake)",
         (bx + 2.54, by + 7.0))

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    wire(pg, ng)
    lg = add(ng, (-1, 0), 2.54)
    wire(ng, lg)
    label("EPD_GDR", lg, "L")
    res_down("1M_0603", ng, side="L")
    ps = q1.p("2")
    ns = add(ps, (0, 1), 2.54)
    wire(ps, ns)
    ls = add(ns, (1, 0), 5.08)
    wire(ns, ls)
    label("EPD_RESE", ls, "R")
    res_down("2R2_0603", ns, side="L")
    d_fields = {"Footprint": "Diode_SMD:D_SOD-123", "MPN": "MBR0530T1G", "Manufacturer": "onsemi",
                "LCSC": "C82046", "Description": "Schottky 30V 0.5A SOD-123"}
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    cap_down("1u50", n_gh)
    e_gh = add(n_gh, (1, 0), 7.62)
    wire(n_gh, e_gh)
    label("EPD_PREVGH", e_gh, "R")
    c3 = C("4u7_50", (sw[0], sw[1] - 7.62), "V", side="L")
    wire(sw, c3.p(2))
    nx = add(c3.p(1), (0, -1), 5.08)
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    wire(ny, d1.p("1"))
    e_gl = add(d1.p("2"), (1, 0), 12.7)
    wire(d1.p("2"), e_gl)
    label("EPD_PREVGL", e_gl, "R")
    cap_down("1u50", add(e_gl, (-1, 0), 5.08))

    ly1 = pins_of("FPC-05FB-24PH20")["1"][1]
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    ra, rb = add(p1, (-1, 0), 5.08), n1   # R28 lands directly on the BTN_N node
    wire(p1, ra)
    hres("100R", rb, ra, below=True)
    label("BTN_SW", add(p1, (-1, 0), G), "D")
    cap_down("100n", n1, side="L")

    # ============================ rev 0.6 menu buttons (appended so existing refs stay stable) =====
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    button(bx + 69.22, "SW3", "BTN3_N", "BTN3_SW", False, "DN: IO15, polled.\\nPull-up: R24 10k (MCU)")
    # IO15 net name (R24 strap pull-up doubles as the SW3 pull-up)
    p15 = u1.p("20")
    label("BTN3_N", add(p15, (-1, 0), 2.54), "L")


def main():
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
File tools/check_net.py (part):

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find_part("EPD_CS_N", "+3V3", "100kR")           # e-paper sleep pull-ups
find_part("EPD_RST_N", "+3V3", "100kR")
# programming pogo cluster J4: +3V3, GND, EN, BOOT (BTN3_N), TXD0, RXD0; no BOM, no placement
for pin, nm in ((1, "VREF"), (2, "GND"), (3, "EN"), (4, "BTN3_N"), (5, "TXD0"), (6, "RXD0")):
    expect("J4", pin, nm)
find_part("VREF", "+3V3", "1kR")           # J4.1 is a sense-only VREF; programmer cannot feed +3V3
if flags["J4"] != {"exclude_from_bom", "exclude_from_pos_files"}:
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for r_, l_ in (("D1", "C965860"), ("D5", "C965863")):
    assert comps[r_]["LCSC"] == l_, r_
expect("D6", 1, "+3V3")
for pin, nm, val in ((4, "LED_R", "1kR"), (2, "LED_B", "470R")):
    find_part(nm, net("D6", pin), val)
nc("D6", 3)    # green unused since rev 0.9: IO15 went to CHG_DIS
assert "R33" not in comps, "R33 retired in rev 0.9"
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
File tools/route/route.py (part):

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    T(['U1.5', (25.9, 4.8), (25.75, 4.4), (25.75, 4.1)], 0.15, 'F', '/BTN_N'); V(25.75, 4.1, '/BTN_N')
    T(['C10.2', (24.32, 8.7), (24.15, 9.0), (24.15, 9.5)], 0.3, 'F', GND)
    # SPI escapes: two staggered via columns inside the right pad row
    for pin, net, x in ((29, '/EPD_MOSI', 37.45), (28, '/EPD_SCK', 36.65), (27, '/EPD_CS_N', 37.45),
                        (26, '/EPD_DC', 36.65), (25, '/EPD_RST_N', 37.45)):
        y = r.pp('U1', pin)[1]
        V(x, y, net); T(['U1.%d' % pin, (x, y)], 0.15, 'F', net)
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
